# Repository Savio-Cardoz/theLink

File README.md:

# The Link

**The Link** is an IoT messaging system that enables secure, offline-capable message delivery to ESP32-based devices with E-Ink displays. The system consists of a cloud server backend with mongoDB and an ESP32 client device that provides a reliable, low-power messaging solution.

## Key Features

- **Secure Authentication**: Implements challenge-response authentication using pre-shared secrets and AES encryption
- **Wi-Fi Provisioning**: Supports BLE and SoftAP provisioning for easy device setup
- **Message Persistence**: Stores received messages in ESP32 NVS (50KB allocated) for offline display
- **Cloud Integration**: Messages are stored in MongoDB on Oracle Cloud infrastructure
- **E-Ink Display**: 1.54-inch E-Ink display with optimized text rendering and word-wrapping
- **Offline Capability**: Displays last received message when no new messages are available
- **RESTful API**: HTTP-based communication between device and server with JSON payloads

## System Architecture

- **Server**: Python Flask application running on Oracle Cloud with MongoDB storage
- **Client**: ESP32 microcontroller with E-Ink display and Wi-Fi connectivity
- **Communication**: Secure HTTP requests with bearer token authentication
- **Display**: Custom word-wrapping algorithm ensures clean text presentation

The device automatically loads stored messages at startup and fetches new messages from the cloud, providing a seamless messaging experience even in intermittent connectivity scenarios.

# Getting started

## Prerequisites
- ESP-IDF v5.5.3 or later
- Python 3.10 or later
- ESP32 development board with 1.54inch E-Ink display
- Oracle Cloud server with MongoDB for message storage

## Hardware Setup

- Connect the E-Ink display to the ESP32 according to the pinout in `main/app_main.cpp`
- Ensure the ESP32 is connected to a power source and USB for flashing

## Server Setup
- Deploy the server code in `Server/` to an Oracle Cloud instance, I've used a ubuntu vm
- Copy `Server/config.json.example` to `Server/config.json` and update with your MongoDB URI and pre-shared secret
- Install Python dependencies: `pip install -r Server/server_requirements.txt`
- Configure MongoDB for message storage
- Update the server endpoint in `main/app_main.cpp` if necessary
- Config NGINX to forward requests on 80 to the application
```
server {
    listen 80;
    server_name _;
    
    location / {
        proxy_pass http://127.0.0.1:8000;
        proxy_set_header Host $host;
        proxy_set_header X-Real-IP $remote_addr;
        proxy_set_header X-Forwarded-For $proxy_add_x_forwarded_for;
        proxy_set_header X-Forwarded-Proto $scheme;
    }
}
```

# How to build and run

## Building the ESP32 Firmware
1. Install ESP-IDF and set up the environment
2. Navigate to the project directory: `cd /path/to/theLink`
3. Configure the project: `idf.py menuconfig`
   - Set Wi-Fi provisioning options
   - Configure server endpoint under "Example Configuration"
4. Build the project: `idf.py build`
5. Flash to ESP32: `idf.py -p /dev/ttyUSB0 flash`
6. Monitor the output: `idf.py -p /dev/ttyUSB0 monitor`

## Running the Server
1. On your Oracle Cloud instance, create a python virtual environment.
2. Activate the virtual environment and install Python dependencies: `pip install -r requirements.txt`
3. Setup the config.json file with the MONGODB connection and a Pre-shared secret
4. Run the authentication server: `python auth.py`
5. The server will listen for ESP32 connections and message requests
6. Test the server with the `test_client.py` script.

## Device Operation
- On first boot, the ESP32 will enter provisioning mode. I have used the SoftAP mode.
- Use the provisioning app from espressif to connect to Wi-Fi AP created by the ESP32. You may have to enable softAP configuration in the apps settings.
- The provisioning key is `abcd1234`. 
- Once provisioned, the device will periodically check for new messages
- Messages are displayed on the E-Ink display
- Stored messages are loaded at startup if no new messages are available

# How to test
## Test message transmission
- Run the script `test_client.py` to connect and send messages to the server. The client tests the complete process of authentication and message transmission.
- Flash the ESP32, it should run and GET messages from the server. This message is parsed and the message should be displayed

## Testing Steps
1. Start the server: `python Server/auth.py`
2. Send a test message: `python Server/test_client.py`
3. Verify the message is stored in MongoDB
4. Power on the ESP32 and provision Wi-Fi
5. Check the E-Ink display for the received message
6. Test offline functionality: Power cycle the ESP32 without new messages - it should display the last stored message

## Troubleshooting
- If provisioning fails, check BLE/SoftAP configuration in menuconfig
- If messages don't display, verify the server endpoint and authentication
- Check serial logs for error messages

# TODO
- Currently all messages in the DB are being returned to the device. This will lead to memory shortage if too many messages pile up. Read only a single message from the server.
- Add ability to send a 200x200 array to display images

# Note:
**This application was built on top of the WiFi Prov example from the ESP-IDF directory, I'm including the information from that example down below**

| Supported Targets | ESP32 | ESP32-C2 | ESP32-C3 | ESP32-C5 | ESP32-C6 | ESP32-C61 | ESP32-S2 | ESP32-S3 |
| ----------------- | ----- | -------- | -------- | -------- | -------- | --------- | -------- | -------- |

# Wi-Fi Provisioning Manager Example

(See the README.md file in the upper level 'examples' directory for more information about examples.)

`wifi_prov_mgr` example demonstrates the usage of `wifi_provisioning` manager component for building a provisioning application.

For this example, BLE is chosen as the default mode of transport, over which the provisioning related communication is to take place. NimBLE has been configured as the default host, but you can also switch to Bluedroid using menuconfig -> Components -> Bluetooth -> Bluetooth Host.

> Note: Since ESP32-S2 does not support BLE, the SoftAP will be the default mode of transport in that case. Even for ESP32, you can change to SoftAP transport from menuconfig.

In the provisioning process the device is configured as a Wi-Fi station with specified credentials. Once configured, the device will retain the Wi-Fi configuration, until a flash erase is performed.

Right after provisioning is complete, BLE is turned off and disabled to free the memory used by the BLE stack. Though, that is specific to this example, and the user can choose to keep BLE stack intact in their own application.

`wifi_prov_mgr` uses the following components :
* `wifi_provisioning` : provides manager, data structures and protocomm endpoint handlers for Wi-Fi configuration
* `protocomm` : for protocol based communication and secure session establishment
* `protobuf` : Google's protocol buffer library for serialization of protocomm data structures
* `bt` : ESP32 BLE stack for transport of protobuf packets

This example can be used, as it is, for adding a provisioning service to any application intended for IoT.

> Note: If you use this example code in your own project, in BLE mode, then remember to enable the BT stack and BTDM BLE control settings in your SDK configuration (e.g. by using the `sdkconfig.defaults` file from this project).

## How to use example

### Hardware Required

Example should be able to run on any commonly available ESP32/ESP32-S2 development board.

### Application Required

Provisioning applications are available for various platforms. See below

#### Platform : Android

For Android, a provisioning application along with source code is available on GitHub : [esp-idf-provisioning-android](https://github.com/espressif/esp-idf-provisioning-android)

#### Platform : iOS

For iOS, a provisioning application along with source code is available on GitHub : [esp-idf-provisioning-ios](https://github.com/espressif/esp-idf-provisioning-ios)

#### Platform : Linux / Windows / macOS

To install the dependency packages needed, please refer to the top level [README file](../../README.md#running-test-python-script-pytest).

`esp_prov` supports BLE and SoftAP transport for Linux, MacOS and Windows platforms. For BLE, however, if dependencies are not met, the script falls back to console mode and requires another application through which the communication can take place. The `esp_prov` console will guide you through the provisioning process of locating the correct BLE GATT services and characteristics, the values to write, and input read values.

### Configure the project

```
idf.py menuconfig
```
* Set the BLE/Soft AP transport under "Example Configuration" options. ESP32-S2 will have only SoftAP option (SoftAP option cannot be used if IPv4 is disabled in lwIP)

### Build and Flash

Build the project and flash it to the board, then run monitor tool to view serial output:

```
idf.py -p PORT flash monitor
```

(To exit the serial monitor, type ``Ctrl-]``.)

See the Getting Started Guide for full steps to configure and use ESP-IDF to build projects.

## Example Output

```
I (445) app: Starting provisioning
I (1035) app: Provisioning started
I (1045) wifi_prov_mgr: Provisioning started with service name : PROV_261FCC
```

Make sure to note down the BLE device name (starting with `PROV_`) displayed in the serial monitor log (eg. PROV_261FCC). This will depend on the MAC ID and will be unique for every device.

In a separate terminal run the `esp_prov.py` script under `$IDP_PATH/tools/esp_prov` directory (make sure to replace `myssid` and `mypassword` with the credentials of the AP to which the device is supposed to connect to after provisioning). Assuming default example configuration, which uses the protocomm security scheme 1 with PoP-based (proof-of-possession) authentication :

```
python esp_prov.py --transport ble --service_name PROV_261FCC --sec_ver 1 --pop abcd1234 --ssid myssid --passphrase mypassword
```

For security version 2, the following command can be used:
```
python esp_prov.py --transport ble --service_name PROV_261FCC --sec_ver 2 --sec2_username wifiprov --sec2_pwd abcd1234 --ssid myssid --passphrase mypassword
```

Above command will perform the provisioning steps, and the monitor log should display something like this :

```
I (39725) app: Received Wi-Fi credentials
    SSID     : myssid
    Password : mypassword
.
.
.
I (45335) esp_netif_handlers: sta ip: 192.168.43.243, mask: 255.255.255.0, gw: 192.168.43.1
I (45345) app: Provisioning successful
I (45345) app: Connected with IP Address:192.168.43.243
I (46355) app: Hello World!
I (47355) app: Hello World!
I (48355) app: Hello World!
I (49355) app: Hello World!
.
.
.
I (52315) wifi_prov_mgr: Provisioning stopped
.
.
.
I (52355) app: Hello World!
I (53355) app: Hello World!
I (54355) app: Hello World!
I (55355) app: Hello World!
```

**Note:** For generating the credentials for security version 2 (`SRP6a` salt and verifier) for the device-side, the following example command can be used. The output can then directly be used in this example.

The config option `CONFIG_EXAMPLE_PROV_SEC2_DEV_MODE` should be enabled for the example and in `main/app_main.c`, the macro `EXAMPLE_PROV_SEC2_USERNAME` should be set to the same username used in the salt-verifier generation.

```log
$ python esp_prov.py --transport softap --sec_ver 2 --sec2_gen_cred --sec2_username wifiprov --sec2_pwd abcd1234
==== Salt-verifier for security scheme 2 (SRP6a) ====
static const char sec2_salt[] = {
    0x03, 0x6e, 0xe0, 0xc7, 0xbc, 0xb9, 0xed, 0xa8, 0x4c, 0x9e, 0xac, 0x97, 0xd9, 0x3d, 0xec, 0xf4
};

static const char sec2_verifier[] = {
    0x7c, 0x7c, 0x85, 0x47, 0x65, 0x08, 0x94, 0x6d, 0xd6, 0x36, 0xaf, 0x37, 0xd7, 0xe8, 0x91, 0x43,
    0x78, 0xcf, 0xfd, 0x61, 0x6c, 0x59, 0xd2, 0xf8, 0x39, 0x08, 0x12, 0x72, 0x38, 0xde, 0x9e, 0x24,
    .
    .
    .
    0xe6, 0xf6, 0x53, 0xc8, 0x31, 0xa8, 0x78, 0xde, 0x50, 0x40, 0xf7, 0x62, 0xde, 0x36, 0xb2, 0xba
};

```

### QR Code Scanning

Enabling `CONFIG_EXAMPLE_PROV_SHOW_QR` will display a QR code on the serial terminal, which can be scanned from the ESP Provisioning phone apps to start the Wi-Fi provisioning process.

The monitor log should display something like this :

```
I (1462) app: Provisioning started
I (1472) app: Scan this QR code from the provisioning application for Provisioning.
I (1472) QRCODE: Encoding below text with ECC LVL 0 & QR Code Version 10
I (1482) QRCODE: {"ver":"v1","name":"PROV_EA69FC","pop":"abcd1234","transport":"ble"}
GAP procedure initiated: advertise; disc_mode=2 adv_channel_map=0 own_addr_type=0 adv_filter_policy=0 adv_itvl_min=256 adv_itvl_max=256

  █▀▀▀▀▀█ ▀▀▀█▄█   ▀▀▄ █▄ ▀ █▀▀▀▀▀█
  █ ███ █  ▀▄█ █▄ ▀▄█ ▄██ █ █ ███ █
  █ ▀▀▀ █  ▄▀█▀▄▀ ▀█▄▀  ██  █ ▀▀▀ █
  ▀▀▀▀▀▀▀ █▄▀ █▄█▄█ ▀ █ █ ▀ ▀▀▀▀▀▀▀
  ▀▀ ▀▀ ▀  ▀▄ ▀▄ ▄▀▀▀█ ▀▄ ▀ ▀▄▄ ▄▄▀
  ███▄█▄▀ █▀  ▀▀▀▀▄▄█   █▀ █  ▄█▄█▀
  ▀███▀ ▀▄▄██ ▄▄██▄ ▀▀▀▀   ▄▀█ ▀▄▄▀
  ▄███  ▀██▀▀ ▄ ▄█▄▀▀█▄ ▀▄▀▄▄█  ▄
  ▀█▀ █▄▀▀ ▀▀█▀▀ █▀▄▀▄▀ ▄█  ███▄ ██
  ██▀█  ▀▄█ █▄▀▄███▀▄▀█ ▀█ █▀▀ ▀▄▄▀
  █▄▀▄█▀▀ ▀▄ ▀▄▄█▄▀▀█▄█▄█▀▀█ ▀▄ ▄▀
  █ ▄█▄ ▀ ▄▀ █▄  ▀█▄█▄▀▀█▀█ ▄█ ▀▄▄█
  ▀▀▀▀  ▀ █▀█▀▀▄▄██▄█▀█ ▀██▀▀▀█▄▄▀
  █▀▀▀▀▀█   ▄█▀▀▀██ ▄▀▄ █▄█ ▀ █ ▄ ▄
  █ ███ █ █ ▀▄█▀▀█▀▄█▄▄ ▀██▀▀▀▀▄▄▀▀
  █ ▀▀▀ █ ▄█ ▀ ▄█▀█ █▀ ▀▀███▄▀█ █▄█
  ▀▀▀▀▀▀▀ ▀  ▀  ▀▀ ▀     ▀▀▀▀▀▀

I (1702) app: If QR code is not visible, copy paste the below URL in a browser.
https://espressif.github.io/esp-jumpstart/qrcode.html?data={"ver":"v1","name":"PROV_EA69FC","pop":"abcd1234","transport":"ble"}
```

### Wi-Fi Scanning

Provisioning manager also supports providing real-time Wi-Fi scan results (performed on the device) during provisioning. This allows the client side applications to choose the AP for which the device Wi-Fi station is to be configured. Various information about the visible APs is available, like signal strength (RSSI) and security type, etc. Also, the manager now provides capabilities information which can be used by client applications to determine the security type and availability of specific features (like `wifi_scan`).

When using the scan based provisioning, we don't need to specify the `--ssid` and `--passphrase` fields explicitly:

```
python esp_prov.py --transport ble --service_name PROV_261FCC --pop abcd1234
```

See below the sample output from `esp_prov` tool on running above command:

```
Connecting...
Connected
Getting Services...
Security scheme determined to be : 1

==== Starting Session ====
==== Session Established ====

==== Scanning Wi-Fi APs ====
++++ Scan process executed in 1.9967520237 sec
++++ Scan results : 5

++++ Scan finished in 2.7374596596 sec
==== Wi-Fi Scan results ====
S.N. SSID                              BSSID         CHN RSSI AUTH
[ 1] MyHomeWiFiAP                      788a20841996    1 -45  WPA2_PSK
[ 2] MobileHotspot                     7a8a20841996   11 -46  WPA2_PSK
[ 3] MyHomeWiFiAP                      788a208daa26   11 -54  WPA2_PSK
[ 4] NeighborsWiFiAP                   8a8a20841996    6 -61  WPA2_PSK
[ 5] InsecureWiFiAP                    dca4caf1227c    7 -74  Open

Select AP by number (0 to rescan) : 1
Enter passphrase for MyHomeWiFiAP :

==== Sending Wi-Fi Credentials to Target ====
==== Wi-Fi Credentials sent successfully ====

==== Applying Wi-Fi Config to Target ====
==== Apply config sent successfully ====

==== Wi-Fi connection state  ====
==== WiFi state: Connected ====
==== Provisioning was successful ====
```

### Interactive Provisioning

`esp_prov` supports interactive provisioning. You can trigger the script with a simplified command and input the necessary details
(`Proof-of-possession` for security scheme 1 and `SRP6a username`, `SRP6a password` for security scheme 2) as the provisioning process advances.

The command `python esp_prov.py --transport ble --sec_ver 1` gives out the following sample output:

```
Discovering...
==== BLE Discovery results ====
S.N. Name                              Address
[ 1] PROV_4C33E8                       01:02:03:04:05:06
[ 1] BT_DEVICE_SBC                     0A:0B:0C:0D:0E:0F
Select device by number (0 to rescan) : 1
Connecting...
Getting Services...
Proof of Possession required:

==== Starting Session ====
==== Session Established ====

==== Scanning Wi-Fi APs ====
++++ Scan process executed in 3.8695244789123535 sec
++++ Scan results : 2

++++ Scan finished in 4.4132080078125 sec
==== Wi-Fi Scan results ====
S.N. SSID                              BSSID         CHN RSSI AUTH
[ 1] MyHomeWiFiAP                      788a20841996    1 -45  WPA2_PSK
[ 2] MobileHotspot                     7a8a20841996   11 -46  WPA2_PSK

Select AP by number (0 to rescan) : 1
Enter passphrase for myssid :

==== Sending Wi-Fi Credentials to Target ====
==== Wi-Fi Credentials sent successfully ====

==== Applying Wi-Fi Config to Target ====
==== Apply config sent successfully ====

==== Wi-Fi connection state  ====
==== WiFi state: Connected ====
==== Provisioning was successful ====
```

### Sending Custom Data

The provisioning manager allows applications to send some custom data during provisioning, which may be
required for some other operations like connecting to some cloud service. This is achieved by creating
and registering additional endpoints using the below APIs

```
wifi_prov_mgr_endpoint_create();
wifi_prov_mgr_endpoint_register();
```

In this particular example, we have added an endpoint named "custom-data" which can be tested
by passing the `--custom_data <MyCustomData>` option to the esp\_prov tool. Following output is
expected on success:

```
==== Sending Custom data to esp32 ====
CustomData response: SUCCESS
```

## Troubleshooting

### Provisioning failed

It is possible that the Wi-Fi credentials provided were incorrect, or the device was not able to establish connection to the network, in which the the `esp_prov` script will notify failure (with reason). Serial monitor log will display the failure along with disconnect reason :

```
E (367015) app: Provisioning failed!
    Reason : Wi-Fi AP password incorrect
    Please reset to factory and retry provisioning
```

Once credentials have been applied, even though wrong credentials were provided, the device will no longer go into provisioning mode on subsequent reboots until NVS is erased (see following section).

### Provisioning does not start

If the serial monitor log shows the following :

```
I (465) app: Already provisioned, starting Wi-Fi STA
```

it means either the device has been provisioned earlier with or without success (e.g. scenario covered in above section), or that the Wi-Fi credentials were already set by some other application flashed previously onto your device. On setting the log level to DEBUG this is clearly evident :

```
D (455) wifi_prov_mgr: Found Wi-Fi SSID     : myssid
D (465) wifi_prov_mgr: Found Wi-Fi Password : m********d
I (465) app: Already provisioned, starting Wi-Fi STA
```

To fix this we simple need to erase the NVS partition from flash. First we need to find out its address and size. This can be seen from the monitor log on the top right after reboot.

```
I (47) boot: Partition Table:
I (50) boot: ## Label            Usage          Type ST Offset   Length
I (58) boot:  0 nvs              WiFi data        01 02 00009000 00006000
I (65) boot:  1 phy_init         RF data          01 01 0000f000 00001000
I (73) boot:  2 factory          factory app      00 00 00010000 00124f80
I (80) boot: End of partition table
```

Now erase NVS partition by running the following commands :

```
$IDF_PATH/components/esptool_py/esptool/esptool.py erase_region 0x9000 0x6000
```

### Bluetooth Pairing Request during provisioning

ESP-IDF now has functionality to enforce link encryption requirement while performing GATT write on characteristics of provisioning service. This will however result in a pairing pop-up dialog, if link is not encrypted. This feature is disabled by default. In order to enable this feature, please set `CONFIG_WIFI_PROV_BLE_FORCE_ENCRYPTION=y` in the sdkconfig or select the configuration using "idf.py menuconfig" .

```
Component Config --> Wi-Fi Provisioning Manager --> Force Link Encryption during Characteristic Read/Write

```
Recompiling the application with above changes should suffice to enable this functionality.

### Unsupported platform

If the platform requirement, for running `esp_prov` is not satisfied, then the script execution will fallback to console mode, in which case the full process (involving user inputs) will look like this :

```
==== Esp_Prov Version: v1.0 ====
BLE client is running in console mode
    This could be due to your platform not being supported or dependencies not being met
    Please ensure all pre-requisites are met to run the full fledged client
BLECLI >> Please connect to BLE device `PROV_261FCC` manually using your tool of choice
BLECLI >> Was the device connected successfully? [y/n] y
BLECLI >> List available attributes of the connected device
BLECLI >> Is the service UUID '0000ffff-0000-1000-8000-00805f9b34fb' listed among available attributes? [y/n] y
BLECLI >> Is the characteristic UUID '0000ff53-0000-1000-8000-00805f9b34fb' listed among available attributes? [y/n] y
BLECLI >> Is the characteristic UUID '0000ff51-0000-1000-8000-00805f9b34fb' listed among available attributes? [y/n] y
BLECLI >> Is the characteristic UUID '0000ff52-0000-1000-8000-00805f9b34fb' listed among available attributes? [y/n] y

==== Verifying protocol version ====
BLECLI >> Write following data to characteristic with UUID '0000ff53-0000-1000-8000-00805f9b34fb' :
    >> 56302e31
BLECLI >> Enter data read from characteristic (in hex) :
    << 53554343455353
==== Verified protocol version successfully ====

==== Starting Session ====
BLECLI >> Write following data to characteristic with UUID '0000ff51-0000-1000-8000-00805f9b34fb' :
    >> 10015a25a201220a20ae6d9d5d1029f8c366892252d2d5a0ffa7ce1ee5829312545dd5f2aba057294d
BLECLI >> Enter data read from characteristic (in hex) :
    << 10015a390801aa0134122048008bfc365fad4753dc75912e0c764d60749cb26dd609595b6fbc72e12614031a1089733af233c7448e7d7fb7963682c6d8
BLECLI >> Write following data to characteristic with UUID '0000ff51-0000-1000-8000-00805f9b34fb' :
    >> 10015a270802b2012212204051088dc294fe4621fac934a8ea22e948fcc3e8ac458aac088ce705c65dbfb9
BLECLI >> Enter data read from characteristic (in hex) :
    << 10015a270803ba01221a20c8d38059d5206a3d92642973ac6ba8ac2f6ecf2b7a3632964eb35a0f20133adb
==== Session Established ====

==== Sending Wifi credential to esp32 ====
BLECLI >> Write following data to characteristic with UUID '0000ff52-0000-1000-8000-00805f9b34fb' :
    >> 98471ac4019a46765c28d87df8c8ae71c1ae6cfe0bc9c615bc6d2c
BLECLI >> Enter data read from characteristic (in hex) :
    << 3271f39a
==== Wifi Credentials sent successfully ====

==== Applying config to esp32 ====
BLECLI >> Write following data to characteristic with UUID '0000ff52-0000-1000-8000-00805f9b34fb' :
    >> 5355
BLECLI >> Enter data read from characteristic (in hex) :
    << 1664db24
==== Apply config sent successfully ====

==== Wifi connection state  ====
BLECLI >> Write following data to characteristic with UUID '0000ff52-0000-1000-8000-00805f9b34fb' :
    >> 290d
BLECLI >> Enter data read from characteristic (in hex) :
    << 505f72a9f8521025c1964d7789c4d7edc56aedebd144e1b667bc7c0975757b80cc091aa9f3e95b06eaefbc30290fa1
++++ WiFi state: connected ++++
==== Provisioning was successful ====
```

The write data is to be copied from the console output ```>>``` to the platform specific application and the data read from the application is to be pasted at the user input prompt ```<<``` of the console, in the format (hex) indicated in above sample log.

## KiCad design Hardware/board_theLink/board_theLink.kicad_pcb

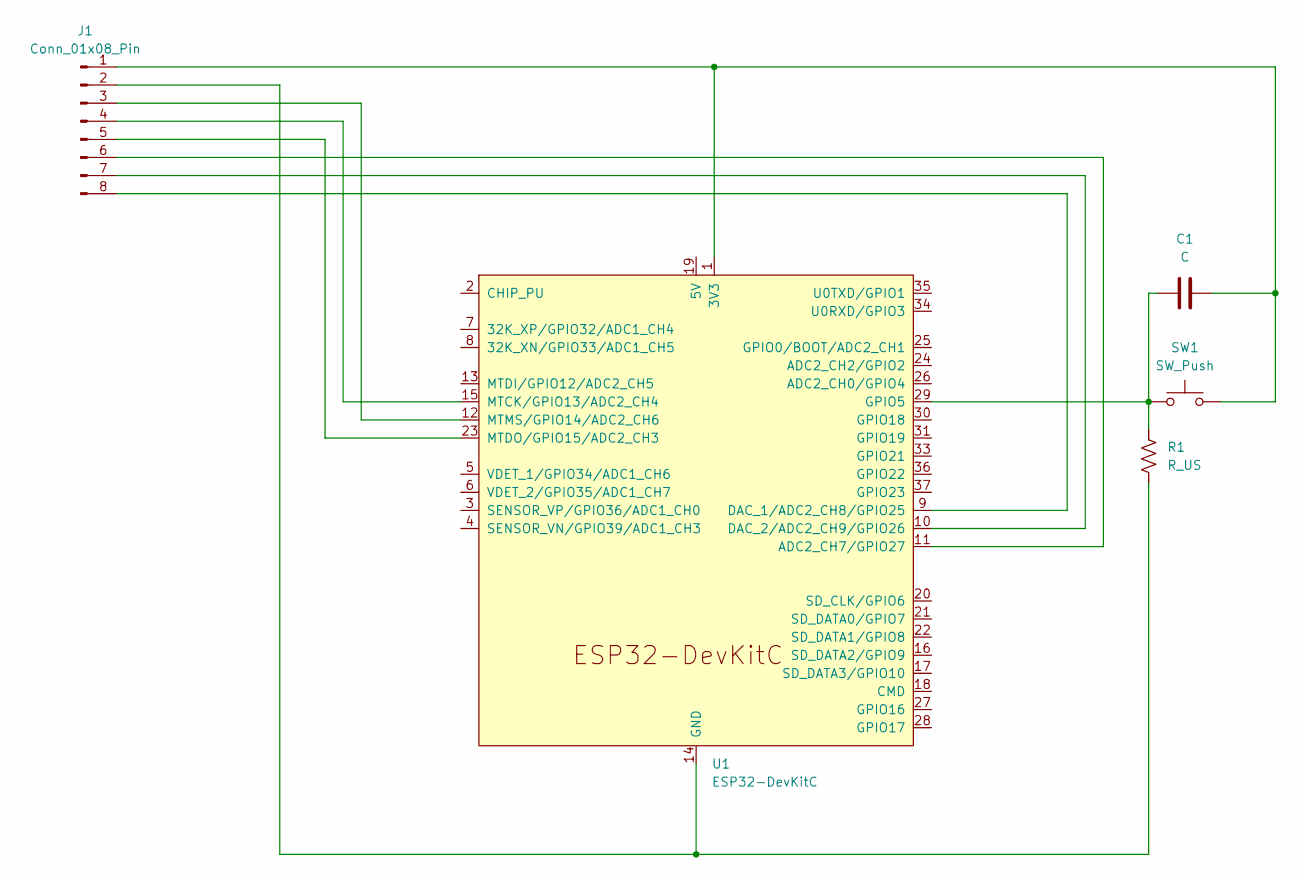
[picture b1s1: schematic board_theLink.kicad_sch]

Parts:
C1: C; C_Disc_D5.1mm_W3.2mm_P5.00mm
J1: Conn_01x08_Pin; PinHeader_1x08_P2.54mm_Vertical
R1: R_US; R_Axial_DIN0309_L9.0mm_D3.2mm_P15.24mm_Horizontal
SW1: SW_Push; SW_PUSH_6mm_H5mm
U1: ESP32-DevKitC

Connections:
unnamed: C1.2, J1.1, SW1.2, U1.1 (3V3)
unnamed: J1.2, R1.2, U1.14 (GND), U1.32 (GND), U1.38 (GND)
unnamed: J1.3, U1.12 (MTMS/GPIO14/ADC2_CH6)
unnamed: J1.4, U1.15 (MTCK/GPIO13/ADC2_CH4)
unnamed: J1.5, U1.23 (MTDO/GPIO15/ADC2_CH3)
unnamed: J1.6, U1.11 (ADC2_CH7/GPIO27)
unnamed: J1.7, U1.10 (DAC_2/ADC2_CH9/GPIO26)
unnamed: J1.8, U1.9 (DAC_1/ADC2_CH8/GPIO25)
unnamed: C1.1, R1.1, SW1.1, U1.29 (GPIO5)

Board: 2 copper layers, 5 parts (0 on the bottom side), 9 nets, no tracks yet.

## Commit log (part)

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2026-02-07 Added test scripts for server client auth and verify
2026-02-07 Added a DELETE method to remove acked messages from the DB
2026-02-24 Get messages and Ack delete from server
2026-03-15 Display to epd
2026-05-17 v1 hardware
2026-05-21 mods for v2 hardware
2026-05-21 use epaper lvgl baseline
2026-05-21 wifi prov added alongside a updating display
2026-05-25 Mqtt connection and http client connect
2026-05-27 Download and store
2026-06-05 define command and run led task on instruction from mqtt
2026-06-06 to be worked upon
2026-06-09 render bin images
2026-06-19 versioning added
2026-06-19 clean up
2026-06-24 RGB LED Notifications added
